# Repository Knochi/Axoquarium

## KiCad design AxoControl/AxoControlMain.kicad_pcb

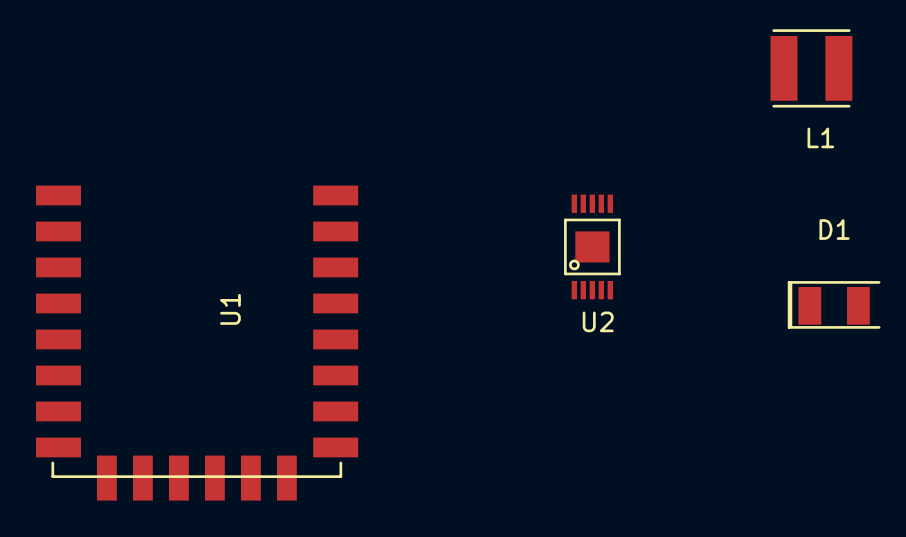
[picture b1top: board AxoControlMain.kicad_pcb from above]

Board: 2 copper layers, 4 parts (0 on the bottom side), 3 nets, no tracks yet.

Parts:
D1: 1A/40V; SMA(DO-214AC)
L1: 15uH; FASTRON_1616FPS
U1: ESP-12E; ESP-12E_SMD
U2: LM25011; HVSSOP-10

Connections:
GND: U2.5, U2.7
unnamed: D1.1, L1.1, U2.9
unnamed: D1.2, U2.8

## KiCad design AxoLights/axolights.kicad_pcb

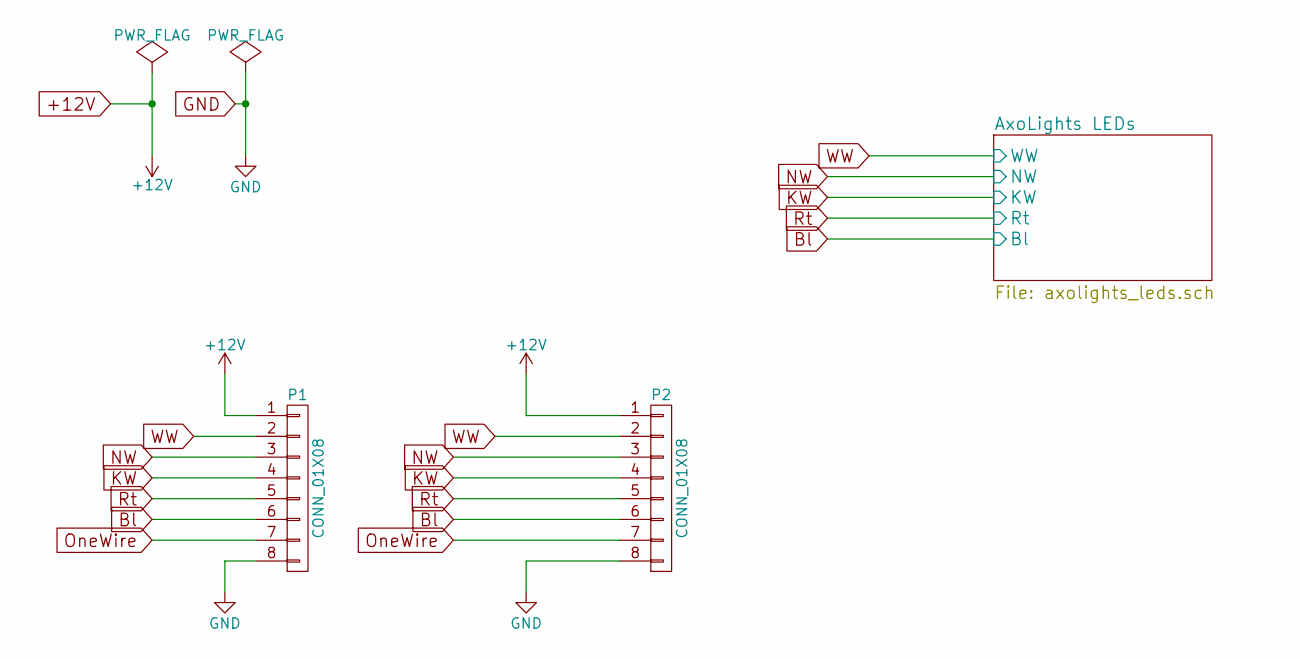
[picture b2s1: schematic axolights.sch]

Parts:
P1, P2: CONN_01X08; JST_XH_B08B-XH-A_08x2.50mm_Straight

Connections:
+12V: P1.1, P2.1; also elsewhere on the board
Bl: P1.6, P2.6; also elsewhere on the board
GND: P1.8, P2.8; also elsewhere on the board
KW: P1.4, P2.4; also elsewhere on the board
NW: P1.3, P2.3; also elsewhere on the board
OneWire: P1.7, P2.7
Rt: P1.5, P2.5; also elsewhere on the board
WW: P1.2, P2.2; also elsewhere on the board

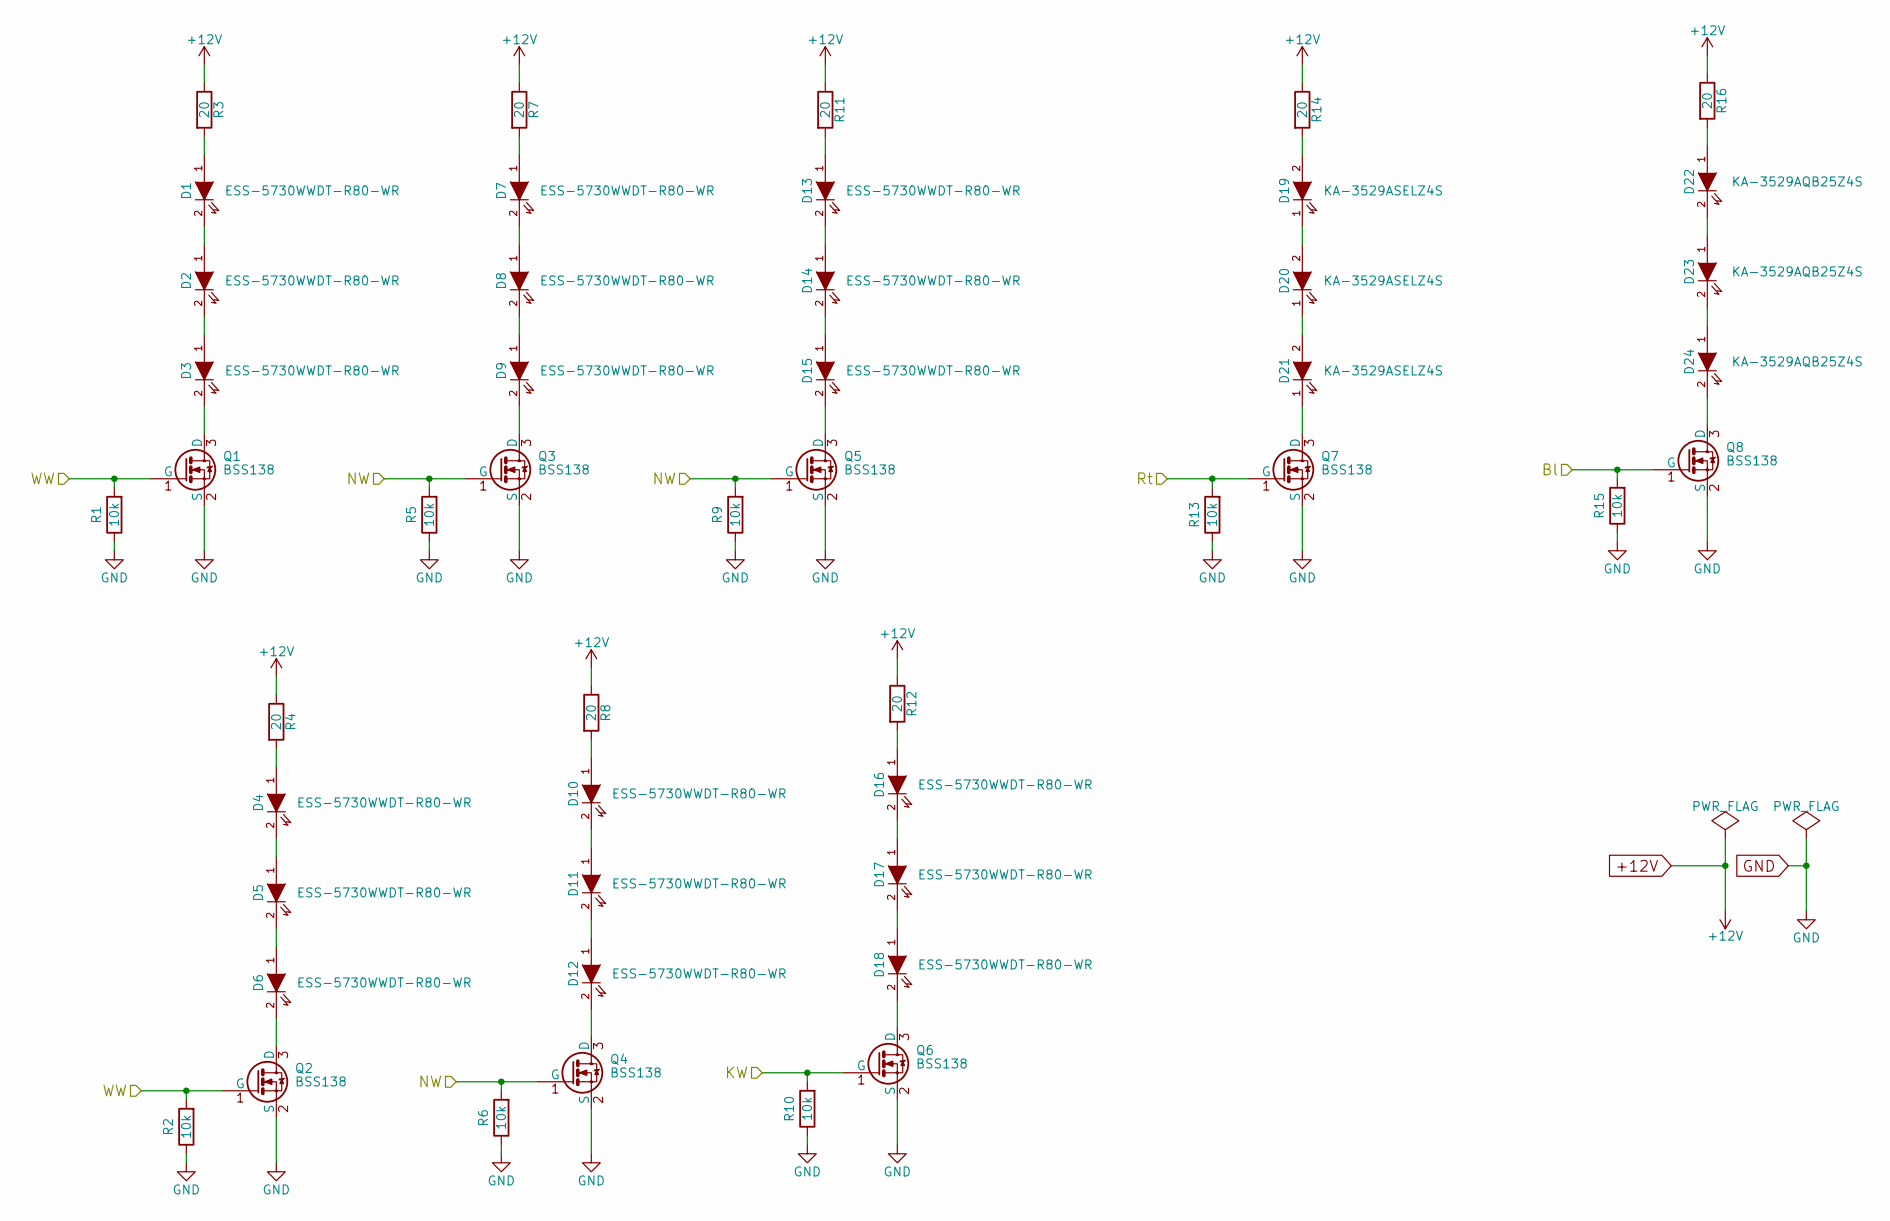
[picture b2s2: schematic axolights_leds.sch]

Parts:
D1, D2, D3, D4, D5, D6, D7, D8, D9, D10, D11, D12, D13, D14, D15, D16, D17, D18: ESS-5730WWDT-R80-WR; LED-5730
D19, D20, D21: KA-3529ASELZ4S
D22, D23, D24: KA-3529AQB25Z4S; LED-3528
Q1, Q2, Q3, Q4, Q5, Q6, Q7, Q8: BSS138; SOT-23
R1, R2, R5, R6, R9, R10, R13, R15: 10k; R_0603
R3, R4, R7, R8, R11, R12, R14, R16: 20; R_1210

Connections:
+12V: R3.1, R4.1, R7.1, R8.1, R11.1, R12.1, R14.1, R16.1; also elsewhere on the board
Bl: Q8.1 (G), R15.2; also elsewhere on the board
GND: Q1.2 (S), Q2.2 (S), Q3.2 (S), Q4.2 (S), Q5.2 (S), Q6.2 (S), Q7.2 (S), Q8.2 (S), R1.1, R2.1, R5.1, R6.1, R9.1, R10.1, R13.1, R15.1; also elsewhere on the board
KW: Q6.1 (G), R10.2; also elsewhere on the board
NW: Q3.1 (G), Q4.1 (G), Q5.1 (G), R5.2, R6.2, R9.2; also elsewhere on the board
unnamed: D1.1 (A), R3.2
unnamed: D1.2 (K), D2.1 (A)
unnamed: D2.2 (K), D3.1 (A)
unnamed: D3.2 (K), Q1.3 (D)
unnamed: D4.1 (A), R4.2
unnamed: D4.2 (K), D5.1 (A)
unnamed: D5.2 (K), D6.1 (A)
unnamed: D6.2 (K), Q2.3 (D)
unnamed: D7.1 (A), R7.2
unnamed: D7.2 (K), D8.1 (A)
unnamed: D8.2 (K), D9.1 (A)
unnamed: D9.2 (K), Q3.3 (D)
unnamed: D10.1 (A), R8.2
unnamed: D10.2 (K), D11.1 (A)
unnamed: D11.2 (K), D12.1 (A)
unnamed: D12.2 (K), Q4.3 (D)
unnamed: D13.1 (A), R11.2
unnamed: D13.2 (K), D14.1 (A)
unnamed: D14.2 (K), D15.1 (A)
unnamed: D15.2 (K), Q5.3 (D)
unnamed: D16.1 (A), R12.2
unnamed: D16.2 (K), D17.1 (A)
unnamed: D17.2 (K), D18.1 (A)
unnamed: D18.2 (K), Q6.3 (D)
unnamed: D19.1 (K), D20.2 (A)
unnamed: D19.2 (A), R14.2
unnamed: D20.1 (K), D21.2 (A)
unnamed: D21.1 (K), Q7.3 (D)
unnamed: D22.1 (A), R16.2
unnamed: D22.2 (K), D23.1 (A)
unnamed: D23.2 (K), D24.1 (A)
unnamed: D24.2 (K), Q8.3 (D)
Rt: Q7.1 (G), R13.2; also elsewhere on the board
WW: Q1.1 (G), Q2.1 (G), R1.2, R2.2; also elsewhere on the board

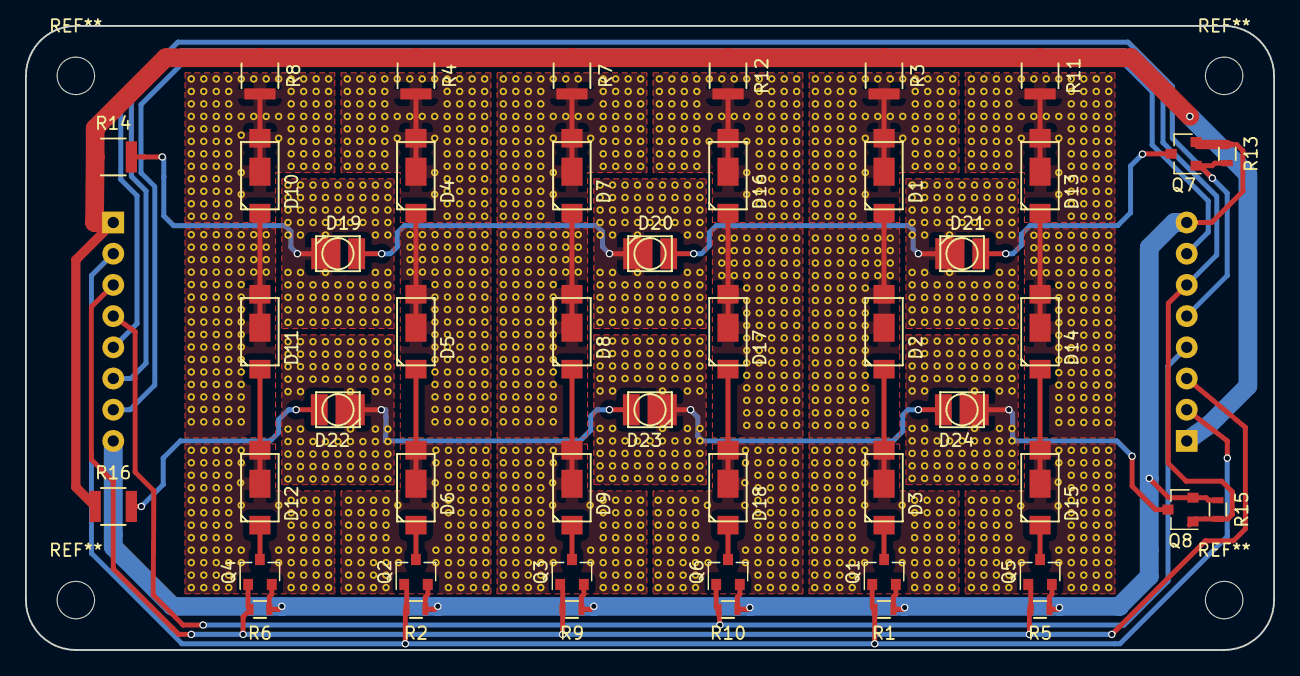
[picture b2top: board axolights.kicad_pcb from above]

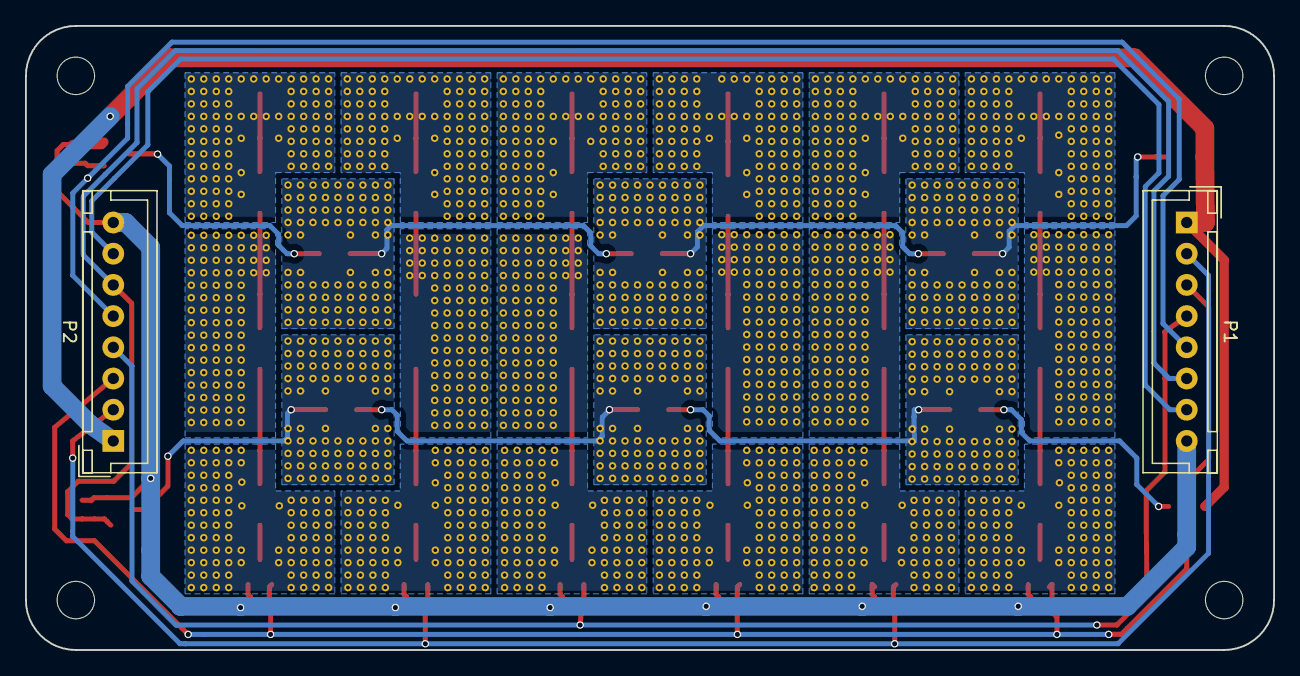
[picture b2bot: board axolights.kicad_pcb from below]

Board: 2 copper layers, 100.0 x 50.0 mm, 50 parts (2 on the bottom side), 40 nets.

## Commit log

2016-07-01 added PLCC-2 LEDs, added Temperature Sensor assembly
2016-07-01 added SOT32 Transistor
2016-07-07 TempSens with additional Tongue, fixed LEDMatrix
2016-07-12 added holder
2016-07-13 created hook
2016-07-13 Updated Holder
2016-07-13 redone Holder
2016-07-15 added fritzing sketch
2016-07-18 Added Firmware for Huzzah Board with Blynk
    First Test succesful
2016-07-19 added Simulation
2016-08-08 added 2-point temperature control
2016-08-08 set to full view
2016-08-14 added cooling pads
2016-08-15 further work on led layout
2016-08-22 bigger leads, cooling fins
2016-08-22 added 0805 res
2016-09-12 added capton for rd/bl
2016-10-03 new Breadboard Design for WeMOS
2016-11-08 fixed rd/bl LED rotation issue
2017-01-25 prepared AQcover
2017-01-25 new geometry
2017-02-19 started kiCad design
2017-02-19 started routing
2017-02-26 added check for One wire devices to fix flickering
2017-02-26 Heatsinks started
    started to layout heatsinking planes for LEDs
2017-06-19 modified side wall geometry
2017-06-29 small changes
2017-06-29 latest changes for production
2017-07-04 added AQxoControl Project
2017-07-24 Added virtual pins to LEDs
    Now able to turn on and off via eventor
2017-11-19 Bugfixes
    fixed FanRPM
    fixed LEDintensity
2017-11-22 fixed.. again
    now it works.. really
2018-03-22 removed fan speed readout for more stability
2018-06-08 initial upload
2023-01-05 added non BLYNK version
2023-01-05 - finished NoBlynk version
2023-01-29 changed default color
2023-02-19 tune light color
2023-11-20 added webserver code
